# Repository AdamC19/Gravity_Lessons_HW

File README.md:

# AC Power Measurement Rasbperry Pi Hat

These are the hardware source files for my AC power measurement system. See also the [software source files](https://github.com/AdamC19/Gravity_Lessons_SW).

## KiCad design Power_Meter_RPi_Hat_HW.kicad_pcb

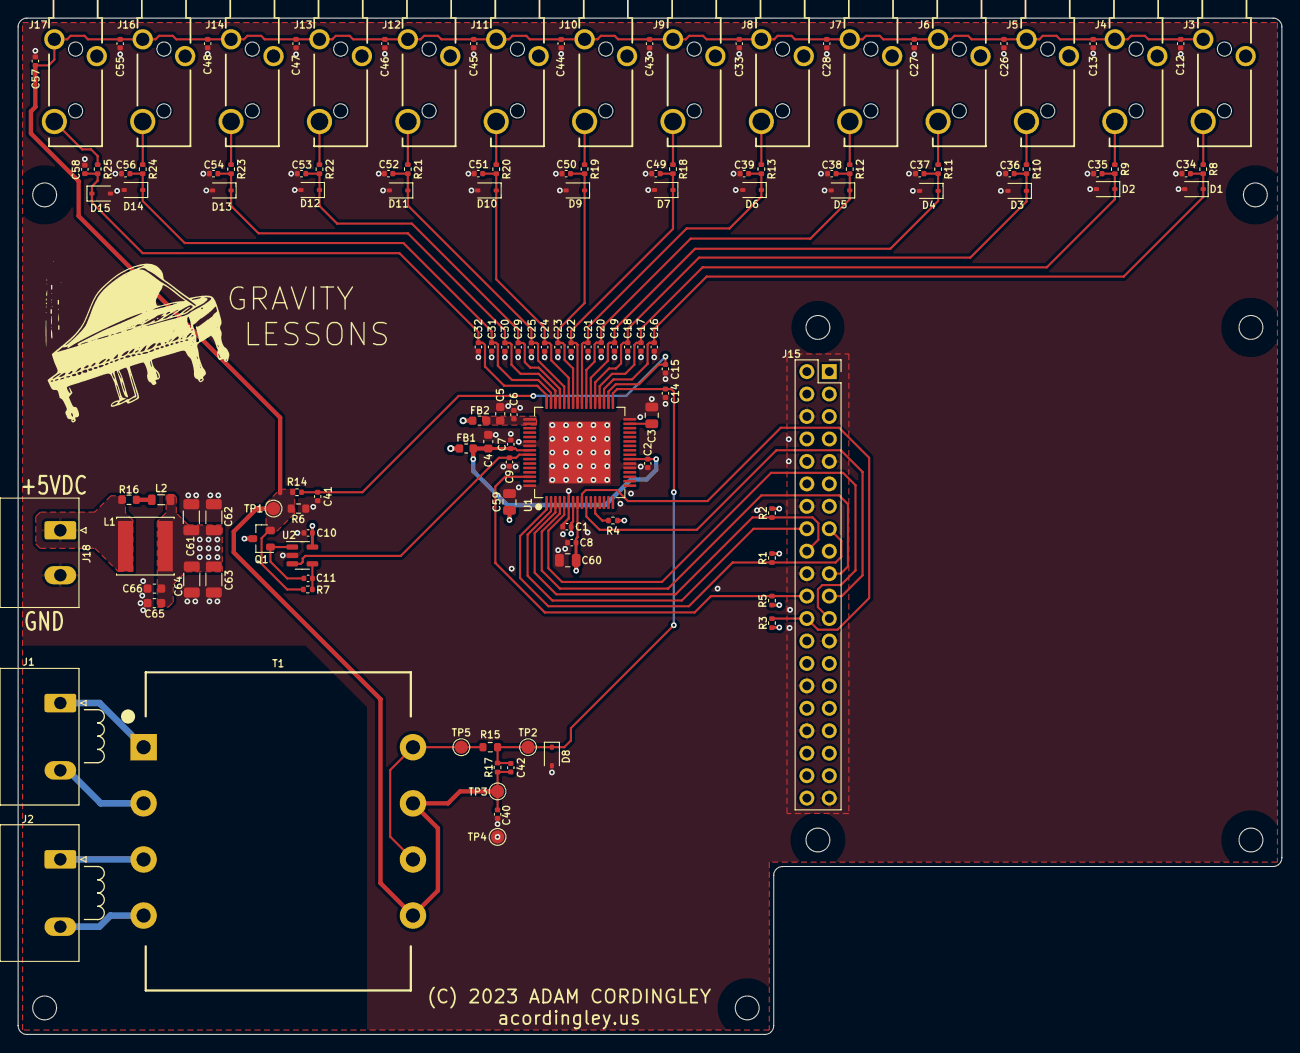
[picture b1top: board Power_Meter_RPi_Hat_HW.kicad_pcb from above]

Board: 4 copper layers, 143.0 x 115.0 mm, 145 parts (0 on the bottom side), 56 nets.

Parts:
C1, C2, C6, C7, C8, C10, C40: 0.1uF; C_0402_1005Metric
C3, C59, C60: 4.7uF; C_0805_2012Metric
C4, C5, C65, C66: 1uF; C_0603_1608Metric
C9: 1000pF; C_0402_1005Metric
C11, C12, C13, C26, C27, C28, C33, C34, C35, C36, C37, C38, C39, C41, C42, C43, C44, C45, C46, C47, C48, C49, C50, C51, C52, C53, C54, C55, C56, C57, C58: 0.01uF; C_0402_1005Metric
C14, C15, C16, C17, C18, C19, C20, C21, C22, C23, C24, C25, C29, C30, C31, C32: 470pF; C_0402_1005Metric
C61, C62, C63, C64: 22uF; C_1206_3216Metric
D1, D2, D3, D4, D5, D6, D7, D8, D9, D10, D11, D12, D13, D14, D15: 4.7V; D_SOD-323
FB1, FB2: 330@100MHz; L_0603_1608Metric
H1, H2, H3, H4, H5, H6, H7, H8: M2.5; MountingHole_2.7mm_M2.5
J1, J2: Conn_01x02; PhoenixContact_GMSTBA_2,5_2-G-7,62_1x02_P7.62mm_Horizontal
J3, J4, J5, J6, J7, J8, J9, J10, J11, J12, J13, J14, J16, J17: SJ-3523; Jack_3.5mm_Kycon_STX-3501-3N
J15: Raspberry_Pi_2_3; PinSocket_2x20_P2.54mm_Vertical
J18: Conn_01x02; PhoenixContact_MSTBA_2,5_2-G-5,08_1x02_P5.08mm_Horizontal
L1: 4.7uH; L_Sunlord_SWPA6045S
L2: 1uH; L_0805_2012Metric
Q1: MMBT3904; SOT-23
R1, R2, R3, R4, R5, R7: 10k; R_0402_1005Metric
R6: 470; R_0603_1608Metric
R8, R9, R10, R11, R12, R13, R14, R17, R18, R19, R20, R21, R22, R23, R24, R25: 1k; R_0402_1005Metric
R15: 6.04k; R_0603_1608Metric
R16: 0.0; R_0603_1608Metric
T1: FS20-055-C2; XFMR_Triad_FS20-055-C2
TP1, TP2, TP3, TP4, TP5: TestPoint; TestPoint_Pad_D1.5mm
U1: AMC7812SPAP; TQFP-64-1EP_10x10mm_P0.5mm_EP7x7mm
U2: TLV9061IDBVR; SOT-23-5

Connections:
+3V3: C1.1, C59.1, J15.1 (3V3), J15.17 (3V3), R1.1, R2.1, R3.1, R4.1, R5.1, U1.7 (IOVDD)
+5V: C8.1, C10.1, C60.1, C61.1, C62.1, C63.1, C64.1, C65.1, C66.1, FB1.1, FB2.1, J15.2 (5V), J15.4 (5V), L1.2, L2.2, Q1.3 (C), U1.8 (DVDD), U2.5 (V+)
/Connectors/DAMP: L2.1, R16.2
/Connectors/I_SNS_IN_0: J3.T, R8.1
/Connectors/I_SNS_IN_1: J4.T, R9.1
/Connectors/I_SNS_IN_2: J5.T, R10.1
/Connectors/I_SNS_IN_3: J6.T, R11.1
/Connectors/I_SNS_IN_4: J7.T, R12.1
/Connectors/I_SNS_IN_5: J8.T, R13.1
/Connectors/I_SNS_IN_6: J9.T, R18.1
/Connectors/I_SNS_IN_7: J10.T, R19.1
/Connectors/I_SNS_IN_8: J11.T, R20.1
/Connectors/I_SNS_IN_9: J12.T, R21.1
/Connectors/I_SNS_IN_10: J13.T, R22.1
/Connectors/I_SNS_IN_11: J14.T, R23.1
/Connectors/I_SNS_IN_12: J16.T, R24.1
/Connectors/I_SNS_IN_13: J17.T, R25.1
/Connectors/MAINS_N1: J1.2, T1.2
/Connectors/MAINS_N2: J2.1, T1.3
/Connectors/MAINS_PH1: J1.1, T1.1
/Connectors/MAINS_PH2: J2.2, T1.4
/Connectors/V-5P0_EXT: J18.1, L1.1, R16.1
/Connectors/V_SNS_PH1: R15.1, T1.5, T1.7, TP5.1
/Inputs and ADC/ADC_REF_CMP: C3.1, U1.31 (ADC-REF-IN/CMP)
/Inputs and ADC/AMC_REF_OUT: C9.1, U1.57 (REF-OUT), U2.3 (+)
/Inputs and ADC/REF_BUF_DRV: C11.1, Q1.1 (B), U2.1
/Inputs and ADC/REF_BUF_FB: C11.2, R7.1, U2.4 (-)
/Inputs and ADC/SPI_SEL: R4.2, U1.12 (SPI/I2C)
/Inputs and ADC/V-5P0_ANLG: C5.1, C6.1, FB2.2, U1.49 (AVDD1), U1.50 (AVDD2)
/Inputs and ADC/V-5P0_DAC: C2.1, C4.1, C7.1, FB1.2, U1.23 (AVCC2), U1.56 (AVCC1)
AMC_ALARMB: J15.22 (GPIO25), R5.2, U1.62 (~ALARM)
AMC_CNVTB: J15.18 (GPIO24), R2.2, U1.3 (~CNVT)
AMC_CSB: J15.24 (~CE0/GPIO8), R3.2, U1.9 (~CS/A0)
AMC_DAVB: J15.16 (GPIO23), U1.2 (~DAV)
AMC_RESETB: J15.15 (GPIO22), R1.2, U1.1 (~RESET)
GND: C1.2, C2.2, C3.2, C4.2, C5.2, C6.2, C7.2, C8.2, C9.2, C10.2, C12.2, C13.2, C14.2, C15.2, C16.2, C17.2, C18.2, C19.2, C20.2, C21.2, C22.2, C23.2, C24.2, C25.2, C26.2, C27.2, C28.2, C29.2, C30.2, C31.2, C32.2, C33.2, C34.2, C35.2, C36.2, C37.2, C38.2, C39.2, C40.2, C41.2, C43.2, C44.2, C45.2, C46.2, C47.2, C48.2, C49.2, C50.2, C51.2, C52.2, C53.2, C54.2, C55.2, C56.2, C57.2, C58.2, C59.2, C60.2, C61.2, C62.2, C63.2, C64.2, C65.2, C66.2, D1.2 (A), D2.2 (A), D3.2 (A), D4.2 (A), D5.2 (A), D6.2 (A), D7.2 (A), D8.2 (A), D9.2 (A), D10.2 (A), D11.2 (A), D12.2 (A), D13.2 (A), D14.2 (A), D15.2 (A), J15.6 (GND), J15.9 (GND), J15.14 (GND), J15.20 (GND), J15.25 (GND), J15.30 (GND), J15.34 (GND), J15.39 (GND), J18.2, R6.2, TP4.1, U1.6 (DGND), U1.21 (AGND4), U1.22 (AGND3), U1.32 (ADC-GND), U1.54 (AGND1), U1.55 (AGND2), U1.64 (DGND2), U1.65 (EP), U2.2 (V-)
I_SNS_IN_0_FILT: C16.1, C34.1, D1.1 (K), R8.2, U1.35 (CH2)
I_SNS_IN_1_FILT: C17.1, C35.1, D2.1 (K), R9.2, U1.36 (CH3)
I_SNS_IN_2_FILT: C18.1, C36.1, D3.1 (K), R10.2, U1.37 (CH4)
I_SNS_IN_3_FILT: C19.1, C37.1, D4.1 (K), R11.2, U1.38 (CH5)
I_SNS_IN_4_FILT: C20.1, C38.1, D5.1 (K), R12.2, U1.39 (CH6)
I_SNS_IN_5_FILT: C21.1, C39.1, D6.1 (K), R13.2, U1.40 (CH7)
I_SNS_IN_6_FILT: C22.1, C49.1, D7.1 (K), R18.2, U1.41 (CH8)
I_SNS_IN_7_FILT: C23.1, C50.1, D9.1 (K), R19.2, U1.42 (CH9)
I_SNS_IN_8_FILT: C24.1, C51.1, D10.1 (K), R20.2, U1.43 (CH10)
I_SNS_IN_9_FILT: C25.1, C52.1, D11.1 (K), R21.2, U1.44 (CH11)
I_SNS_IN_10_FILT: C29.1, C53.1, D12.1 (K), R22.2, U1.45 (CH12)
I_SNS_IN_11_FILT: C30.1, C54.1, D13.1 (K), R23.2, U1.46 (CH13)
I_SNS_IN_12_FILT: C31.1, C56.1, D14.1 (K), R24.2, U1.47 (CH14)
I_SNS_IN_13_FILT: C32.1, C58.1, D15.1 (K), R25.2, U1.48 (CH15)
REF_2P5_BUF: C12.1, C13.1, C26.1, C27.1, C28.1, C33.1, C40.1, C42.2, C43.1, C44.1, C45.1, C46.1, C47.1, C48.1, C55.1, C57.1, J3.S, J4.S, J5.S, J6.S, J7.S, J8.S, J9.S, J10.S, J11.S, J12.S, J13.S, J14.S, J16.S, J17.S, Q1.2 (E), R6.1, R7.2, R14.1, R17.1, T1.6, T1.8, TP1.1, TP3.1
SPI_MISO: J15.21 (MISO0/GPIO9), U1.10 (SDO/A1)
SPI_MOSI: J15.19 (MOSI0/GPIO10), U1.4 (SDI/SDA)
SPI_SCLK: J15.23 (SCLK0/GPIO11), U1.5 (SCLK/SCL)
V_SNS_PH1_FILT: C14.1, C42.1, D8.1 (K), R15.2, R17.2, TP2.1, U1.33 (CH0)
V_SNS_PH2_FILT: C15.1, C41.1, R14.2, U1.34 (CH1)

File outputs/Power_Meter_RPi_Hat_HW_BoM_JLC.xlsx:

Designator | Qty | Comment | Footprint | Description | JLCPCB Part # | Manufacturer | Mfr. Part #
C1, C2, C6, C7, C8, C10, C40 | 7 | 0.1uF | Capacitor_SMD:C_0402_1005Metric | 50V 100nF X7R ±10% 0402 Multilayer Ceramic Capacitors MLCC - SMD/SMT ROHS | C77020 | Murata Electronics | GRM155R71H104KE14D
C3, C59, C60 | 3 | 4.7uF | Capacitor_SMD:C_0805_2012Metric | CAP CER 4.7UF 16V X5R 0805 | C1779 | Samsung Electro-Mechanics | CL21A475KAQNNNE
C4, C5, C65, C66 | 4 | 1uF | Capacitor_SMD:C_0603_1608Metric | CAP CER 1UF 25V X7R 0603 | C29936 | Samsung Electro-Mechanics | CL10B105KA8NNNC
C9 | 1 | 1000pF | Capacitor_SMD:C_0402_1005Metric | CAP CER 1000PF 50V C0G/NPO 0402 | C161523 | Murata | GRM1555C1H102FA01D
C11, C12, C13, C26, C27, C28, C33, C34, C35, C36, C37, C38, C39, C41, C42, C43,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 | 31 | 0.01uF | Capacitor_SMD:C_0402_1005Metric | CAP CER 0.01UF 50V 5% X7R 0402 | C272878 | YAGEO | CC0402JRX7R9BB103
C14, C15, C16, C17, C18, C19, C20, C21, C22, C23, C24, C25, C29, C30, C31, C32 | 16 | 470pF | Capacitor_SMD:C_0402_1005Metric | CAP CER 470PF 50V 5% C0G/NP0 0402 | C307449 | Samsung Electro-Mechanics | CL05C471JB5NNNC
C61, C62, C63, C64 | 4 | 22uF | Capacitor_SMD:C_1206_3216Metric | CAP CER 22UF 16V X5R 1206 | C90146 | Samsung Electro-Mechanics | CL31A226KOHNNNE
D1, D2, D3, D4, D5, D6, D7, D8, D9, D10, D11, D12, D13, D14, D15 | 15 | 4.7V | Diode_SMD:D_SOD-323 | DIODE ZENER 4.7V 300MW SOD323 | C454980 | Nexperia | BZX384-C4V7,115
FB1, FB2 | 2 | 330@100MHz | Inductor_SMD:L_0603_1608Metric | 70mOhm ±25% 330@100MHz 0603 Ferrite Beads ROHS | C710391 | Murata Electronics | BLM18SG331TZ1D
L1 | 1 | 4.7uH | Inductor_SMD:L_Sunlord_SWPA6045S |  | C78804 | Sunlord | SWPA6045S4R7MT
L2 | 1 | 1uH | Inductor_SMD:L_0805_2012Metric |  | C370019 | Sunlord | MPH201206S1R0MT
Q1 | 1 | MMBT3904 | Repowered_TO-SOT-SMD:SOT-23 | XSTR NPN BJT 40Vce 0.1A Ic, SOT-23-3 | C108429 | Nexperia | MMBT3904
R1-R5, R7 | 6 | 10k | Resistor_SMD:R_0402_1005Metric | RES SMD 10K OHM 1% 1/16W 0402 | C144807 | YAGEO | AC0402FR-0710KL
R6 | 1 | 470 | Resistor_SMD:R_0603_1608Metric | RES 470 OHM 1% 1/10W 0603 | C114669 | YAGEO | RC0603FR-07470RL
R8, R9, R10, R11, R12, R13, R14, R17, R18, R19, R20, R21, R22, R23, R24, R25 | 16 | 1k | Resistor_SMD:R_0402_1005Metric | RES SMD 1K OHM 1% 1/16W 0402 | C144789 | YAGEO | AC0402FR-071KL
R15 | 1 | 6.04k | Resistor_SMD:R_0603_1608Metric | RES 6.04K OHM 1% 1/10W 0603 | C862799 | YAGEO | RT0603DRD076K04L
R16 | 1 | 0.0 | Resistor_SMD:R_0603_1608Metric | RES 0.0 OHM JUMPER 1/10W 0603 | C100044 | YAGEO | RC0603FR-070RL
U2 | 1 | TLV9061IDBVR | Package_TO_SOT_SMD:SOT-23-5 | IC, Op-Amp, Single, RRIO 10MHz 0.5pA 1.8V~5.5V, SOT-23-5 | C398358 |  | TLV9061IDBVR

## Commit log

2023-09-09 Add gitignore and readme
2023-09-09 Fix readme
2023-09-09 Add CERN license

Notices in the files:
Power_Meter_RPi_Hat_HW.kicad_pcb:
(C) 2023 ADAM CORDINGLEY
